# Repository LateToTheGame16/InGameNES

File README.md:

# InGameNES
 NES console that fits in a game cart

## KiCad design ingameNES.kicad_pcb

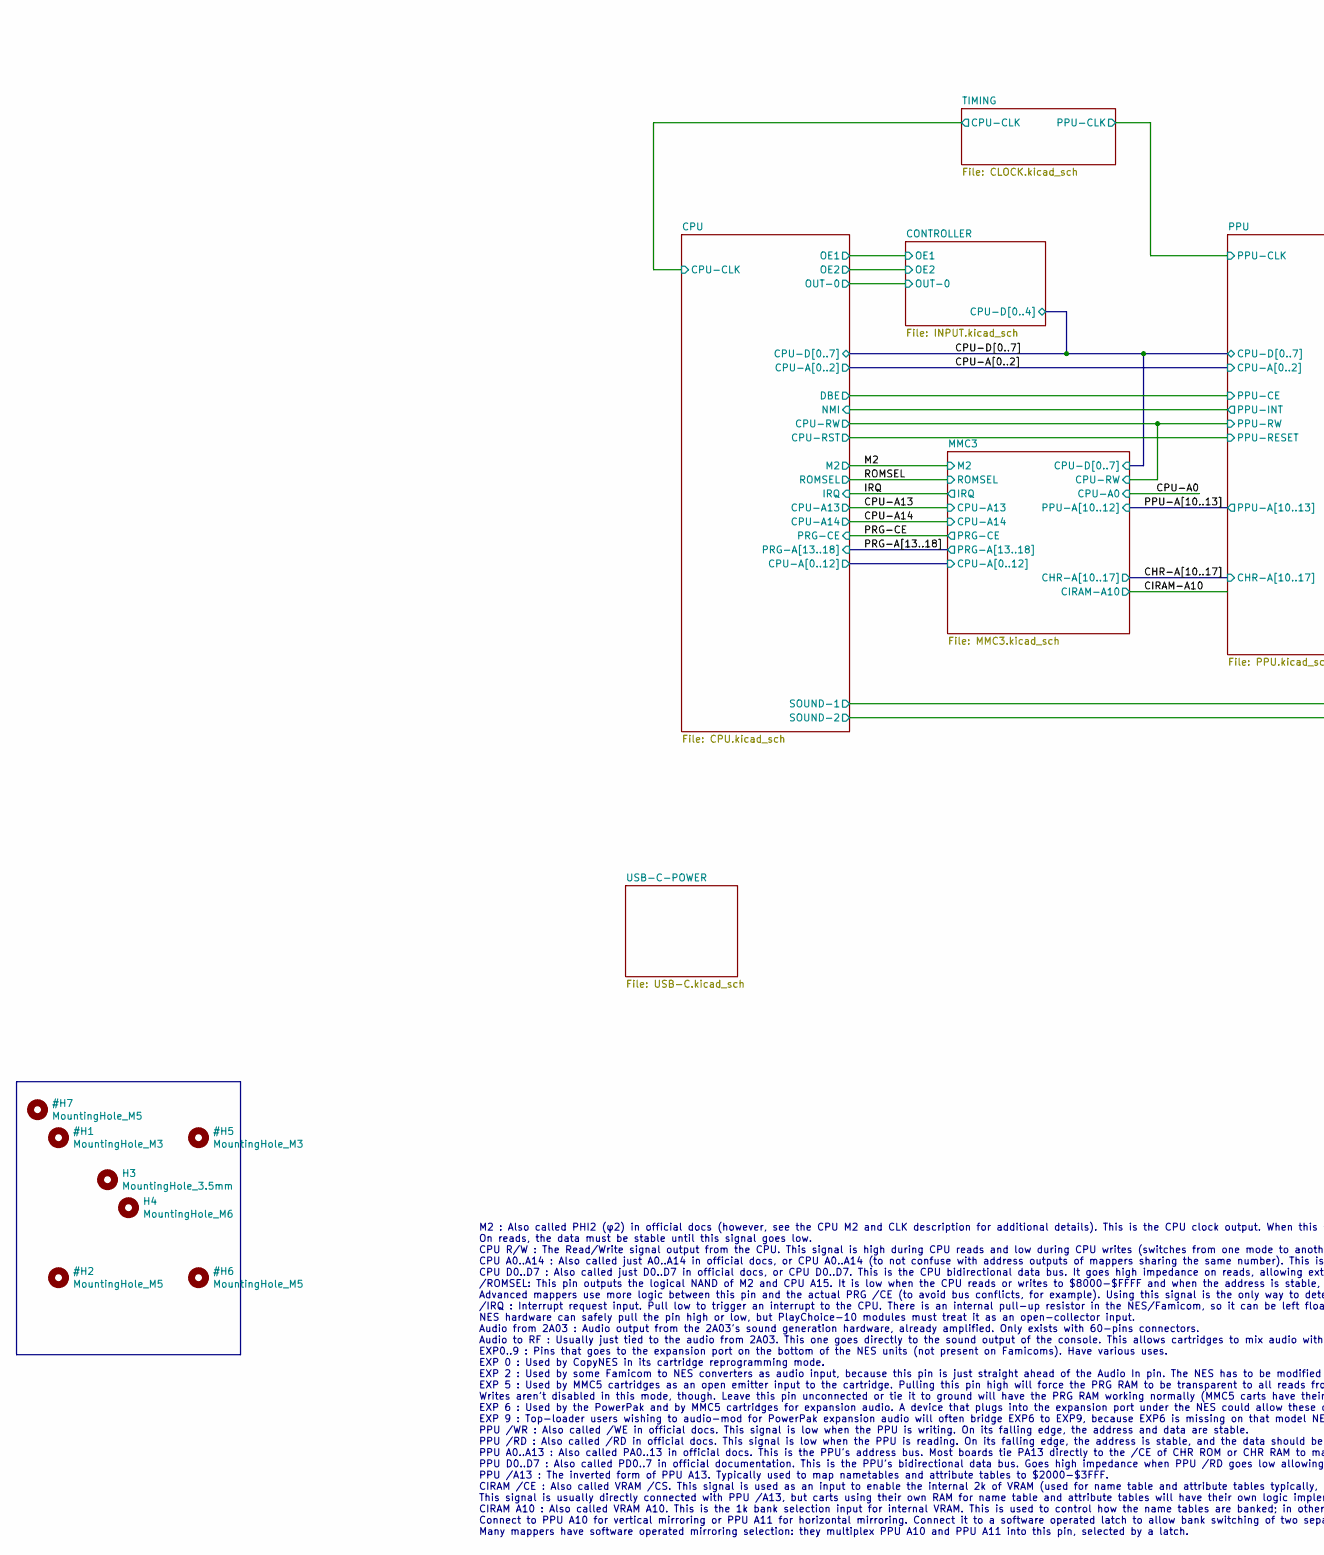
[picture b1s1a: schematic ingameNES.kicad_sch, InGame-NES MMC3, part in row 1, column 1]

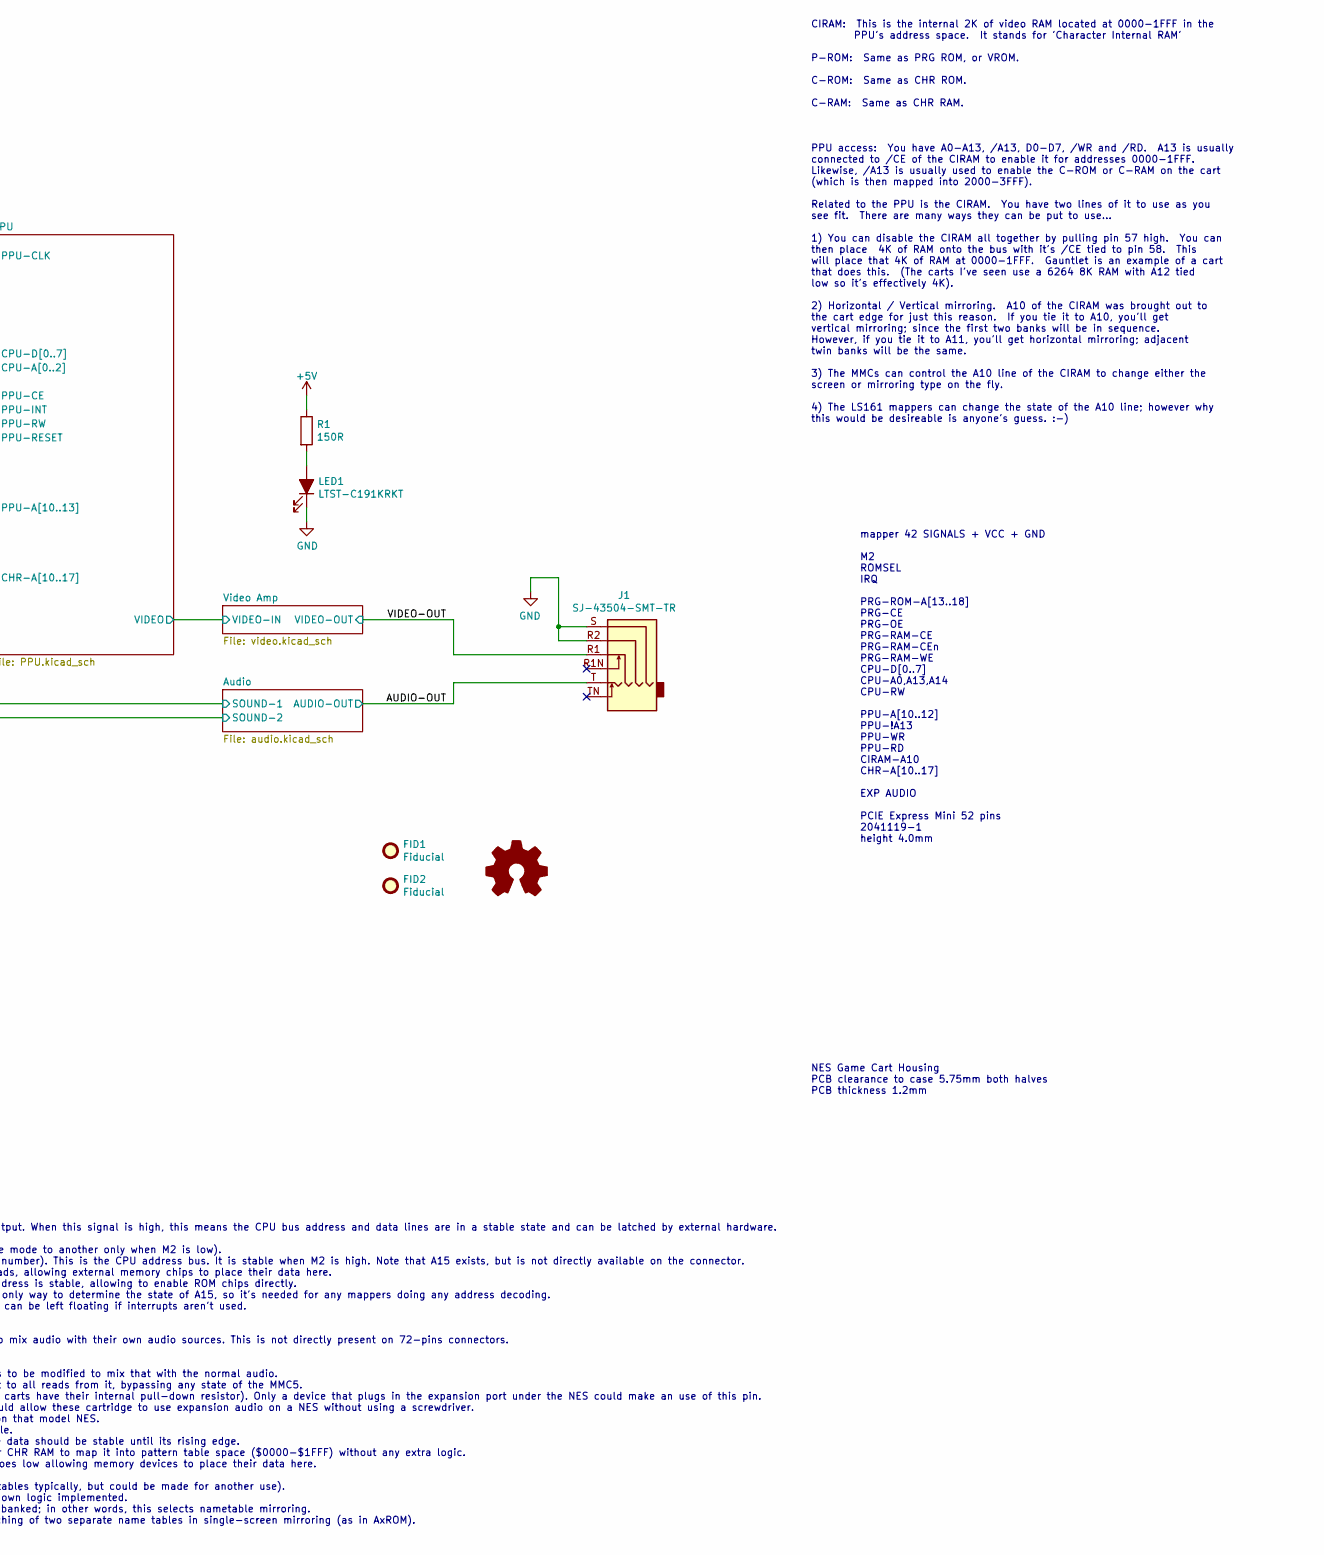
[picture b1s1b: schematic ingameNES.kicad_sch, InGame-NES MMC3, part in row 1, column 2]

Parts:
FID1, FID2: Fiducial; Fiducial_1.5mm_Mask3mm
H3: MountingHole_3.5mm
H4: MountingHole_M6; MountingHole_6.4mm_M6
J1: SJ-43504-SMT-TR; CUI_SJ-43504-SMT-TR; MPN SJ-43504-SMT-TR; Digikey CP-43504SJCT-ND
LED1: LTST-C191KRKT; LED_0603_1608Metric; MPN LTST-C191KRKT; Digikey 160-1447-1-ND
R1: 150R; R_0603_1608Metric; MPN RC0603FR-07150RL; Digikey 311-150HRCT-ND

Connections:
/AUDIO-OUT: J1.T; also elsewhere on the board
/VIDEO-OUT: J1.R1; also elsewhere on the board
unnamed: LED1.2 (A), R1.2

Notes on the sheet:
mapper 42 SIGNALS + VCC + GND M2 ROMSEL IRQ PRG-ROM-A[13..18] PRG-CE PRG-OE PRG-RAM-CE PRG-RAM-CEn PRG-RAM-WE CPU-D[0..7] CPU-A0,A13,A14 CPU-RW PPU-A[10..12] PPU-!A13 PPU-WR PPU-RD CIRAM-A10 CHR-A[10..17] EXP AUDIO PCIE Express Mini 52 pins 2041119-1 height 4.0mm
CIRAM: This is the internal 2K of video RAM located at 0000-1FFF in the PPU's address space. It stands for 'Character Internal RAM' P-ROM: Same as PRG ROM, or VROM. C-ROM: Same as CHR ROM. C-RAM: Same as CHR RAM. PPU access: You have A0-A13, /A13, D0-D7, /WR and /RD. A13 is usually connected to /CE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
M2 : Also called PHI2 (φ2) in official docs (however, see the CPU M2 and CLK description for additional details). This is the CPU clock output. When this signal is high, this means the CPU bus address and data lines are in a stable state and can be latched by external hardware. On reads, the data m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
NES Game Cart Housing PCB clearance to case 5.75mm both halves PCB thickness 1.2mm

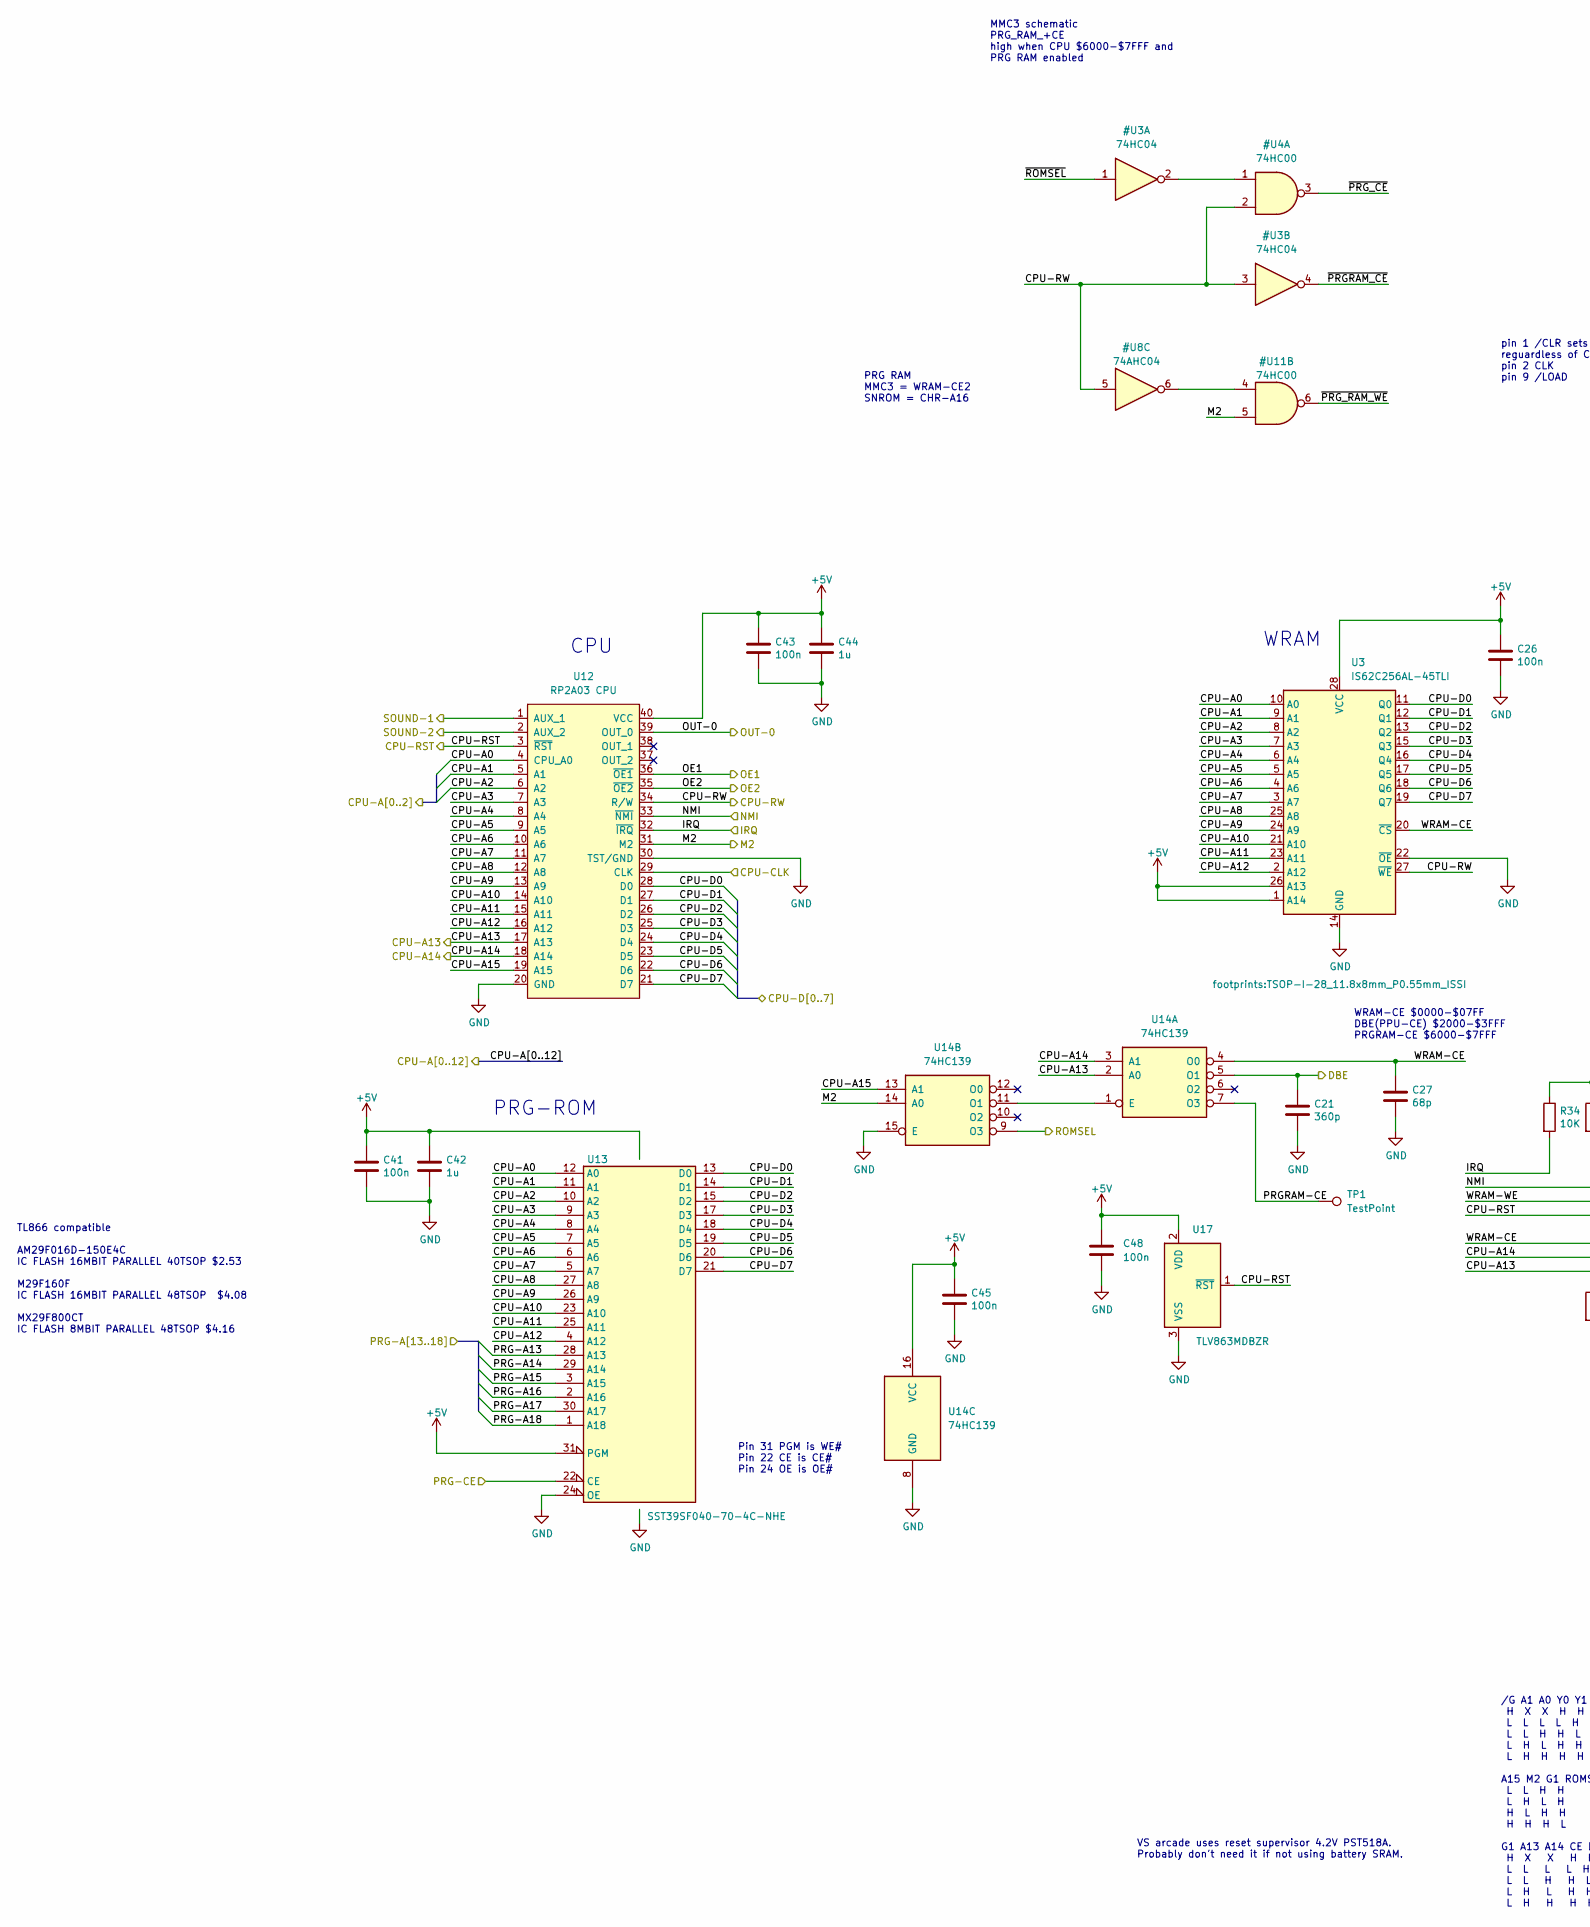
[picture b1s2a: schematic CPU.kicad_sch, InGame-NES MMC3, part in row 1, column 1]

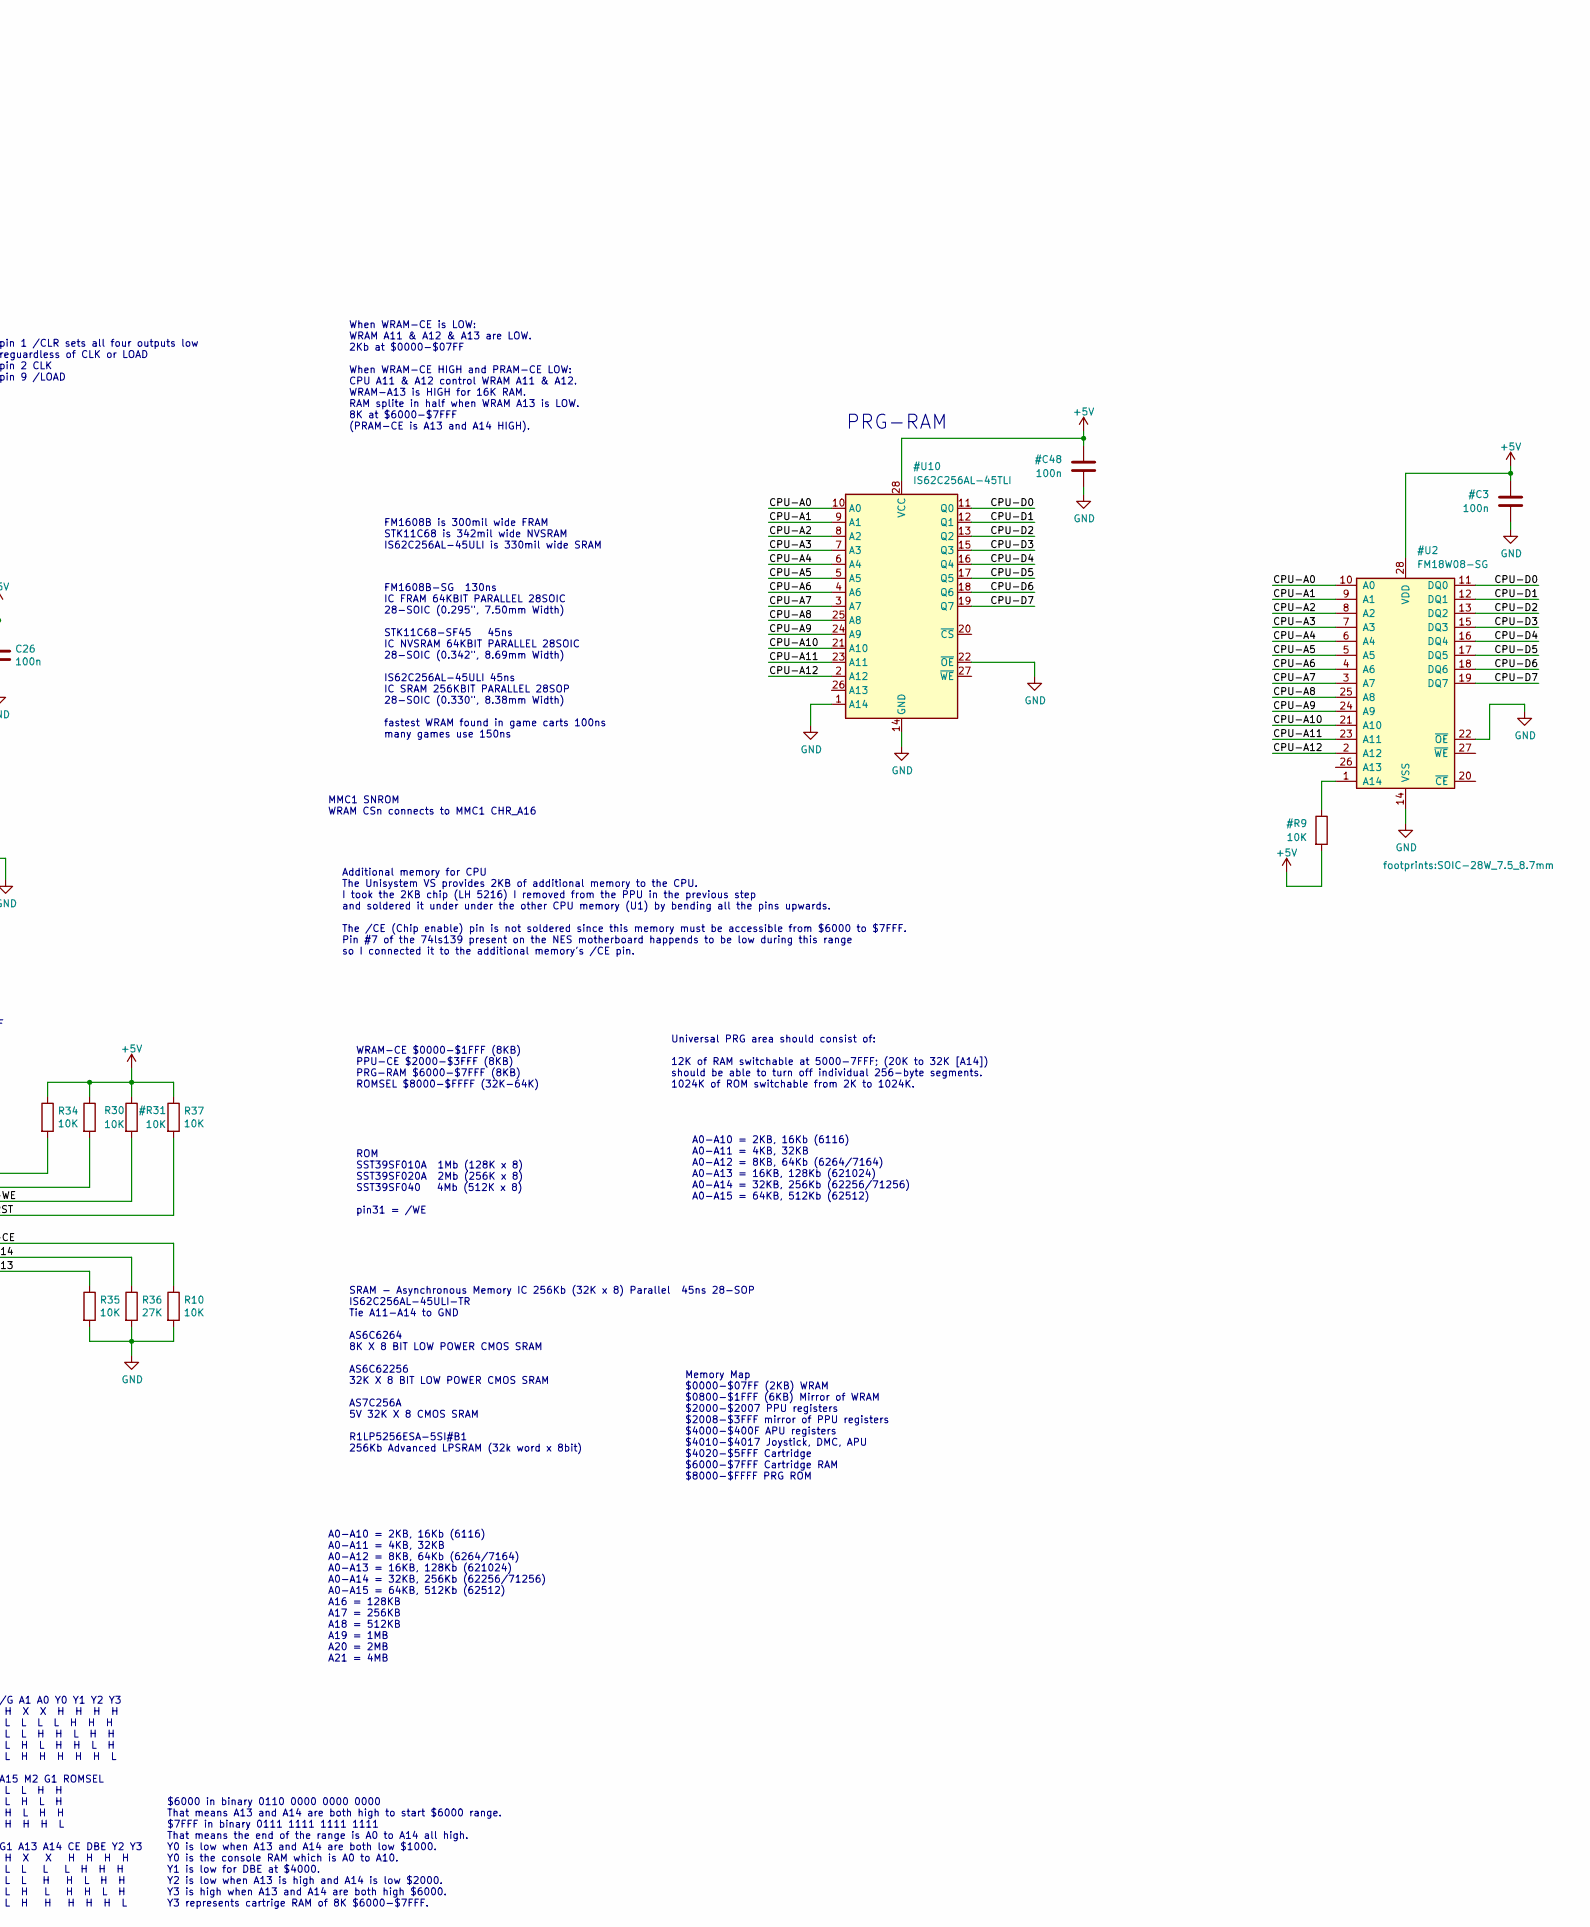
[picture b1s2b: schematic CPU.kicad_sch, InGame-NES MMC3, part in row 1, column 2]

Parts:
C21: 360p; C_0603_1608Metric; MPN C0603C361J5GAC7867; Digikey 399-15397-1-ND
C26, C41, C43, C45, C48: 100n; C_0402_1005Metric; MPN CL05B104KO5NNWC; Digikey 1276-1509-2-ND
C27: 68p; C_0402_1005Metric; MPN CC0402JRNPO9BN680; Digikey 311-1340-1-ND
C42, C44: 1u; C_0402_1005Metric; MPN GRM155R61A105KE15D; Digikey 490-3890-2-ND
R10, R30, R34, R35, R37: 10K; R_0402_1005Metric; MPN ERJ-2RKF1002X; Digikey P10.0KLCT-ND
R36: 27K; R_0402_1005Metric; MPN RC0402JR-0727KL; Digikey 311-27KJRCT-ND
TP1: TestPoint; TestPoint_Pad_D1.5mm
U3: IS62C256AL-45TLI; TSOP-I-28_11.8x8mm_P0.55mm_ISSI; MPN IS62C256AL-45TLI; Digikey 706-1109-ND
U12: RP2A03 CPU; DIP-40_W15.24mm; MPN ED40DT; Digikey ED3048-5-ND
U13: SST39SF040-70-4C-NHE; SOCKET-PLCC-32-SMD; MPN SST39SF040-70-4C-NHE; Digikey SST39SF040-70-4C-NHE-ND
U14: 74HC139; TSSOP-16_4.4x5mm_P0.65mm; MPN SN74HC139PWR; Digikey 296-8231-1-ND
U17: TLV863MDBZR; SOT-23; MPN TLV863MDBZR; Digikey 296-29707-1-ND

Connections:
/Audio/SOUND-1: U12.1 (AUX_1); also elsewhere on the board
/Audio/SOUND-2: U12.2 (AUX_2); also elsewhere on the board
/CONTROLLER/OE1: U12.36 (~OE1); also elsewhere on the board
/CONTROLLER/OE2: U12.35 (~OE2); also elsewhere on the board
/CONTROLLER/OUT-0: U12.39 (OUT_0); also elsewhere on the board
/CPU/CPU-A15: U12.19 (A15), U14.13 (A1)
/CPU/CPU-RST: R37.2, U12.3 (~RST), U17.1 (~RST); also elsewhere on the board
/CPU/DBE: C21.2, U14.5 (O1); also elsewhere on the board
/CPU/NMI: R30.2, U12.33 (~NMI); also elsewhere on the board
/CPU/PRGRAM-CE: TP1.1, U14.7 (O3)
/CPU/WRAM-CE: C27.2, R10.1, U3.20 (~CS), U14.4 (O0)
unnamed: U14.1 (E), U14.11 (O1)

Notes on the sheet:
FM1608B-SG 130ns IC FRAM 64KBIT PARALLEL 28SOIC 28-SOIC (0.295", 7.50mm Width) STK11C68-SF45 45ns IC NVSRAM 64KBIT PARALLEL 28SOIC 28-SOIC (0.342", 8.69mm Width) IS62C256AL-45ULI 45ns IC SRAM 256KBIT PARALLEL 28SOP 28-SOIC (0.330", 8.38mm Width) fastest WRAM found in game carts 100ns many games use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
PRG RAM MMC3 = WRAM-CE2 SNROM = CHR-A16
PRG-ROM
CPU
TL866 compatible AM29F016D-150E4C IC FLASH 16MBIT PARALLEL 40TSOP $2.53 M29F160F IC FLASH 16MBIT PARALLEL 48TSOP $4.08 MX29F800CT IC FLASH 8MBIT PARALLEL 48TSOP $4.16
pin 1 /CLR sets all four outputs low reguardless of CLK or LOAD pin 2 CLK pin 9 /LOAD
Additional memory for CPU The Unisystem VS provides 2KB of additional memory to the CPU. I took the 2KB chip (LH 5216) I removed from the PPU in the previous step and soldered it under under the other CPU memory (U1) by bending all the pins upwards. The /CE (Chip enable) pin is not soldered since t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
ROM SST39SF010A 1Mb (128K x 8) SST39SF020A 2Mb (256K x 8) SST39SF040 4Mb (512K x 8) pin31 = /WE
Memory Map $0000-$07FF (2KB) WRAM $0800-$1FFF (6KB) Mirror of WRAM $2000-$2007 PPU registers $2008-$3FFF mirror of PPU registers $4000-$400F APU registers $4010-$4017 Joystick, DMC, APU $4020-$5FFF Cartridge $6000-$7FFF Cartridge RAM $8000-$FFFF PRG ROM
Pin 31 PGM is WE# Pin 22 CE is CE# Pin 24 OE is OE#
VS arcade uses reset supervisor 4.2V PST518A. Probably don't need it if not using battery SRAM.
PRG-RAM
Universal PRG area should consist of: 12K of RAM switchable at 5000-7FFF; (20K to 32K [A14]) should be able to turn off individual 256-byte segments. 1024K of ROM switchable from 2K to 1024K.
WRAM-CE $0000-$07FF DBE(PPU-CE) $2000-$3FFF PRGRAM-CE $6000-$7FFF
$6000 in binary 0110 0000 0000 0000 That means A13 and A14 are both high to start $6000 range. $7FFF in binary 0111 1111 1111 1111 That means the end of the range is A0 to A14 all high. Y0 is low when A13 and A14 are both low $1000. Y0 is the console RAM which is A0 to A10. Y1 is low for DBE at $40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
When WRAM-CE is LOW: WRAM A11 & A12 & A13 are LOW. 2Kb at $0000-$07FF When WRAM-CE HIGH and PRAM-CE LOW: CPU A11 & A12 control WRAM A11 & A12. WRAM-A13 is HIGH for 16K RAM. RAM splite in half when WRAM A13 is LOW. 8K at $6000-$7FFF (PRAM-CE is A13 and A14 HIGH).
WRAM
SRAM - Asynchronous Memory IC 256Kb (32K x 8) Parallel 45ns 28-SOP IS62C256AL-45ULI-TR Tie A11-A14 to GND AS6C6264 8K X 8 BIT LOW POWER CMOS SRAM AS6C62256 32K X 8 BIT LOW POWER CMOS SRAM AS7C256A 5V 32K X 8 CMOS SRAM R1LP5256ESA-5SI#B1 256Kb Advanced LPSRAM (32k word x 8bit)
MMC3 schematic PRG_RAM_+CE high when CPU $6000-$7FFF and PRG RAM enabled
FM1608B is 300mil wide FRAM STK11C68 is 342mil wide NVSRAM IS62C256AL-45ULI is 330mil wide SRAM
WRAM-CE $0000-$1FFF (8KB) PPU-CE $2000-$3FFF (8KB) PRG-RAM $6000-$7FFF (8KB) ROMSEL $8000-$FFFF (32K-64K)
/G A1 A0 Y0 Y1 Y2 Y3 H X X H H H H L L L L H H H L L H H L H H L H L H H L H L H H H H H L A15 M2 G1 ROMSEL L L H H L H L H H L H H H H H L G1 A13 A14 CE DBE Y2 Y3 H X X H H H H L L L L H H H L L H H L H H L H L H H L H L H H H H H L
A0-A10 = 2KB, 16Kb (6116) A0-A11 = 4KB, 32KB A0-A12 = 8KB, 64Kb (6264/7164) A0-A13 = 16KB, 128Kb (621024) A0-A14 = 32KB, 256Kb (62256/71256) A0-A15 = 64KB, 512Kb (62512) A16 = 128KB A17 = 256KB A18 = 512KB A19 = 1MB A20 = 2MB A21 = 4MB
A0-A10 = 2KB, 16Kb (6116) A0-A11 = 4KB, 32KB A0-A12 = 8KB, 64Kb (6264/7164) A0-A13 = 16KB, 128Kb (621024) A0-A14 = 32KB, 256Kb (62256/71256) A0-A15 = 64KB, 512Kb (62512)
MMC1 SNROM WRAM CSn connects to MMC1 CHR_A16

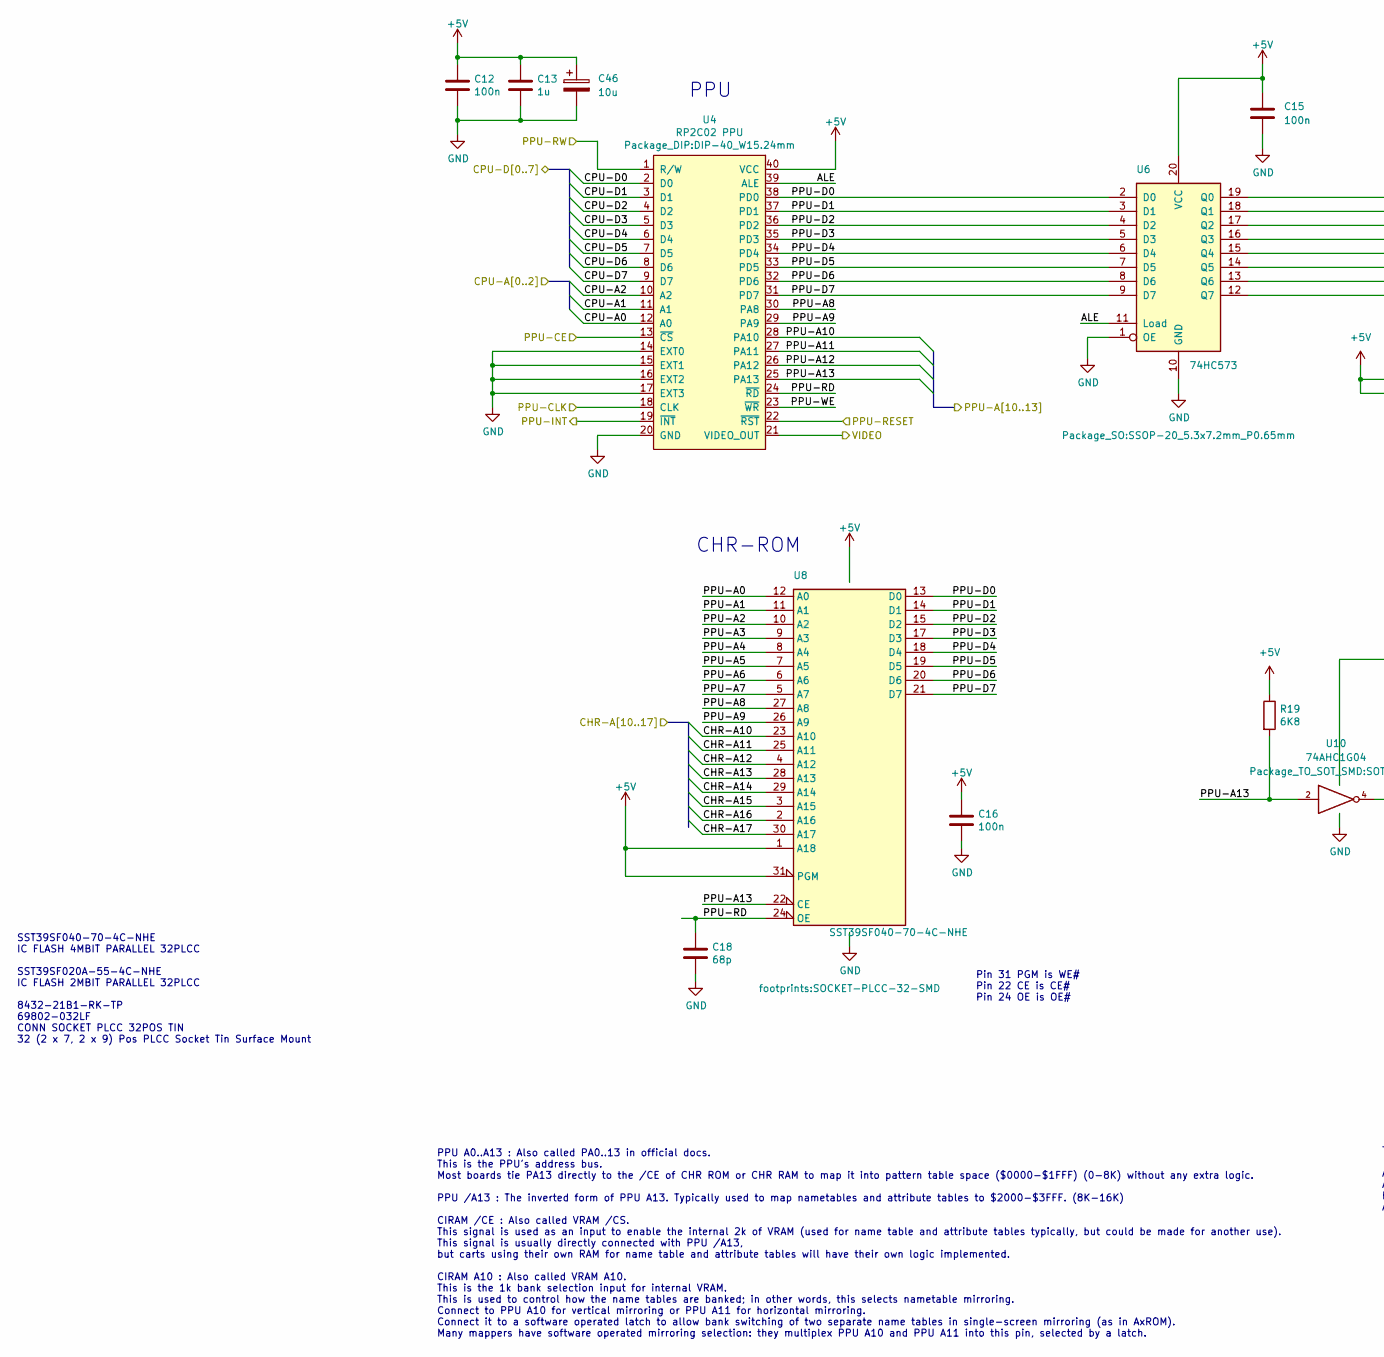
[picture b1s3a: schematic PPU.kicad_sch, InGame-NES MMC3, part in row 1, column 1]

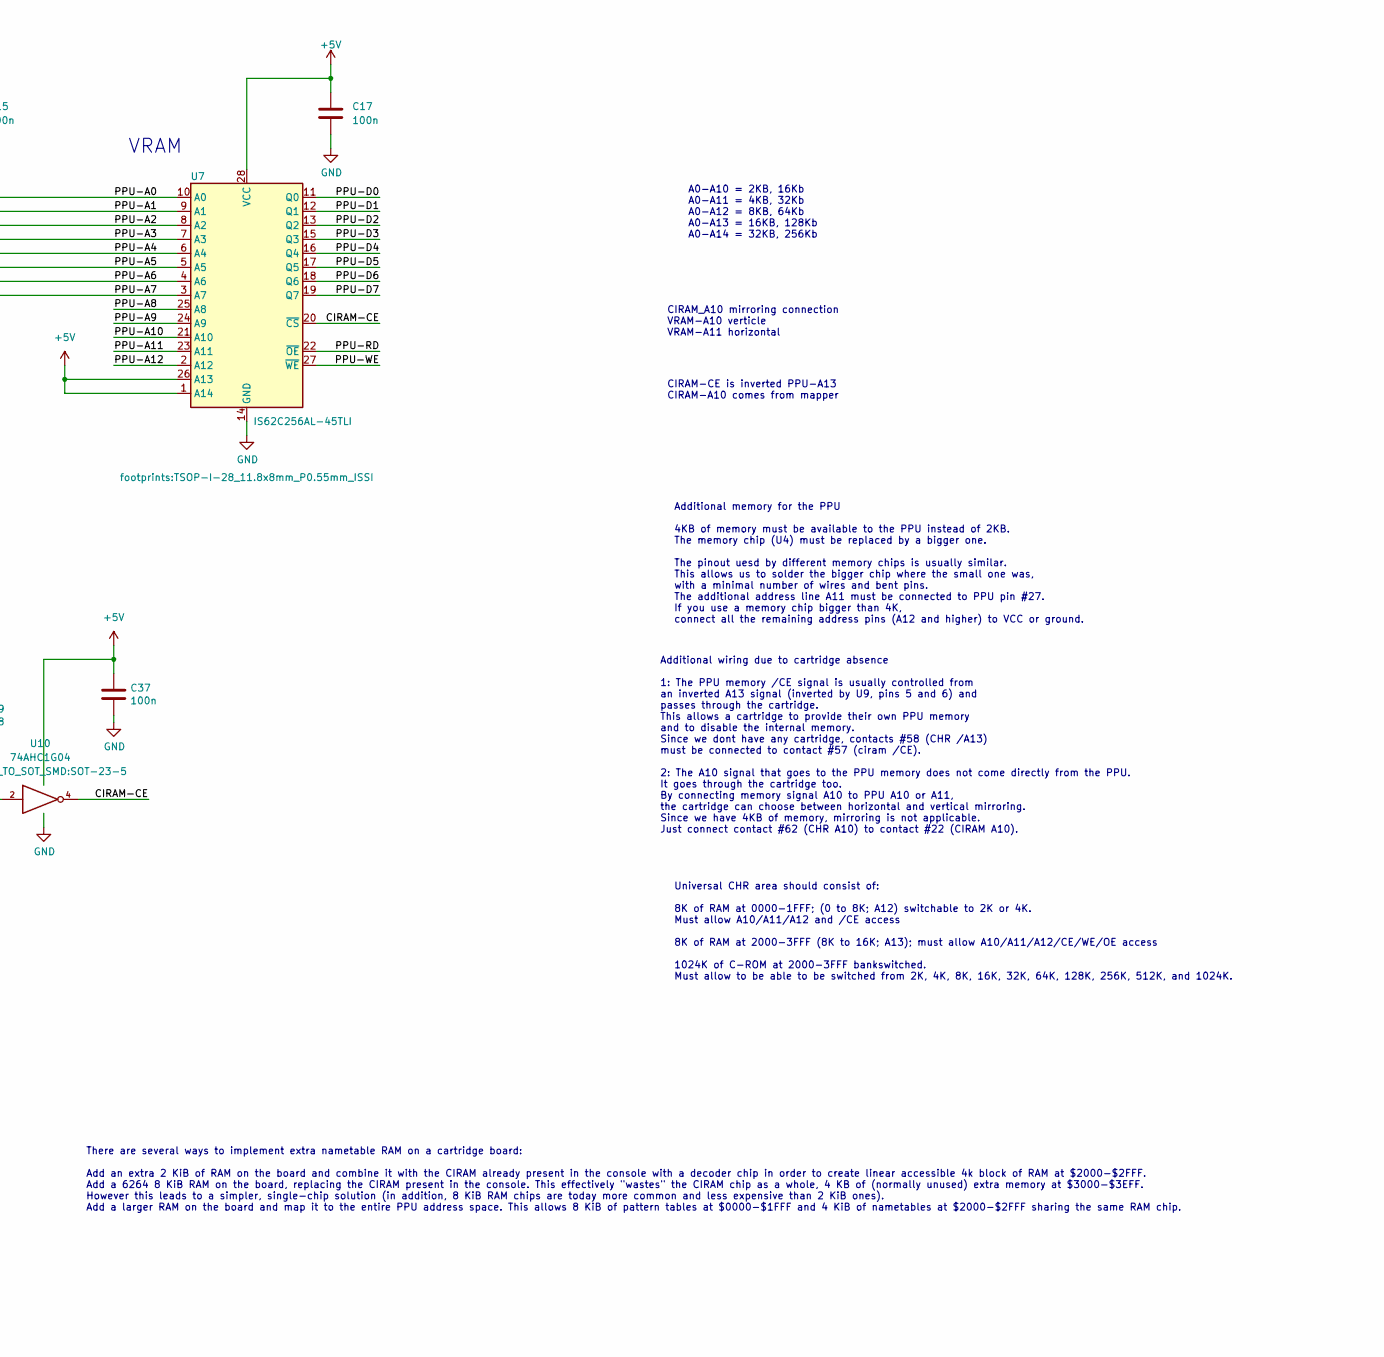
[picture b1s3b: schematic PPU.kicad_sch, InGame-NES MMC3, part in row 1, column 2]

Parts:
C12, C15, C16, C17, C37: 100n; C_0402_1005Metric; MPN CL05B104KO5NNWC; Digikey 1276-1509-2-ND
C13: 1u; C_0402_1005Metric; MPN GRM155R61A105KE15D; Digikey 490-3890-2-ND
C18: 68p; C_0402_1005Metric; MPN CC0402JRNPO9BN680; Digikey 311-1340-1-ND
C46: 10u; CP_EIA-3216-18_Kemet-A; MPN T491A106K010AT; Digikey 399-3684-1-ND
R19: 6K8; R_0402_1005Metric; MPN RC0402FR-076K8L; Digikey 311-6.80KLRCT-ND
U4: RP2C02 PPU; DIP-40_W15.24mm; MPN ED40DT; Digikey ED3048-5-ND
U6: 74HC573; SSOP-20_5.3x7.2mm_P0.65mm; MPN SN74HC573ADBR; Digikey 296-SN74HC573ADBRCT-ND
U7: IS62C256AL-45TLI; TSOP-I-28_11.8x8mm_P0.55mm_ISSI; MPN IS62C256AL-45TLI; Digikey 706-1109-ND
U8: SST39SF040-70-4C-NHE; SOCKET-PLCC-32-SMD; MPN SST39SF040-70-4C-NHE; Digikey SST39SF040-70-4C-NHE-ND
U10: 74AHC1G04; SOT-23-5; MPN SN74AHC1G04DBVR; Digikey 296-1089-1-ND

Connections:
/CPU/CPU-RST: U4.22 (~RST); also elsewhere on the board
/CPU/DBE: U4.13 (~CS); also elsewhere on the board
/CPU/NMI: U4.19 (~INT); also elsewhere on the board
/PPU-A13: R19.2, U4.25 (PA13), U8.22 (CE), U10.2
/PPU/ALE: U4.39 (ALE), U6.11 (Load)
/PPU/CIRAM-CE: U7.20 (~CS), U10.4
/PPU/PPU-A0: U6.19 (Q0), U7.10 (A0), U8.12 (A0)
/PPU/PPU-A1: U6.18 (Q1), U7.9 (A1), U8.11 (A1)
/PPU/PPU-A2: U6.17 (Q2), U7.8 (A2), U8.10 (A2)
/PPU/PPU-A3: U6.16 (Q3), U7.7 (A3), U8.9 (A3)
/PPU/PPU-A4: U6.15 (Q4), U7.6 (A4), U8.8 (A4)
/PPU/PPU-A5: U6.14 (Q5), U7.5 (A5), U8.7 (A5)
/PPU/PPU-A6: U6.13 (Q6), U7.4 (A6), U8.6 (A6)
/PPU/PPU-A7: U6.12 (Q7), U7.3 (A7), U8.5 (A7)
/PPU/PPU-A8: U4.30 (PA8), U7.25 (A8), U8.27 (A8)
/PPU/PPU-A9: U4.29 (PA9), U7.24 (A9), U8.26 (A9)
/PPU/PPU-D0: U4.38 (PD0), U6.2 (D0), U7.11 (Q0), U8.13 (D0)
/PPU/PPU-D1: U4.37 (PD1), U6.3 (D1), U7.12 (Q1), U8.14 (D1)
/PPU/PPU-D2: U4.36 (PD2), U6.4 (D2), U7.13 (Q2), U8.15 (D2)
/PPU/PPU-D3: U4.35 (PD3), U6.5 (D3), U7.15 (Q3), U8.17 (D3)
/PPU/PPU-D4: U4.34 (PD4), U6.6 (D4), U7.16 (Q4), U8.18 (D4)
/PPU/PPU-D5: U4.33 (PD5), U6.7 (D5), U7.17 (Q5), U8.19 (D5)
/PPU/PPU-D6: U4.32 (PD6), U6.8 (D6), U7.18 (Q6), U8.20 (D6)
/PPU/PPU-D7: U4.31 (PD7), U6.9 (D7), U7.19 (Q7), U8.21 (D7)
/PPU/PPU-RD: C18.2, U4.24 (~RD), U7.22 (~OE), U8.24 (OE)
/PPU/PPU-WE: U4.23 (~WR), U7.27 (~WE)
/PPU/VIDEO: U4.21 (VIDEO_OUT); also elsewhere on the board

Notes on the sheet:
SST39SF040-70-4C-NHE IC FLASH 4MBIT PARALLEL 32PLCC SST39SF020A-55-4C-NHE IC FLASH 2MBIT PARALLEL 32PLCC 8432-21B1-RK-TP 69802-032LF CONN SOCKET PLCC 32POS TIN 32 (2 x 7, 2 x 9) Pos PLCC Socket Tin Surface Mount
A0-A10 = 2KB, 16Kb A0-A11 = 4KB, 32Kb A0-A12 = 8KB, 64Kb A0-A13 = 16KB, 128Kb A0-A14 = 32KB, 256Kb
Additional wiring due to cartridge absence 1: The PPU memory /CE signal is usually controlled from an inverted A13 signal (inverted by U9, pins 5 and 6) and passes through the cartridge. This allows a cartridge to provide their own PPU memory and to disable the internal memory. Since we dont have a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
CIRAM_A10 mirroring connection VRAM-A10 verticle VRAM-A11 horizontal
Additional memory for the PPU 4KB of memory must be available to the PPU instead of 2KB. The memory chip (U4) must be replaced by a bigger one. The pinout uesd by different memory chips is usually similar. This allows us to solder the bigger chip where the small one was, with a minimal number of wi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
CHR-ROM
Universal CHR area should consist of: 8K of RAM at 0000-1FFF; (0 to 8K; A12) switchable to 2K or 4K. Must allow A10/A11/A12 and /CE access 8K of RAM at 2000-3FFF (8K to 16K; A13); must allow A10/A11/A12/CE/WE/OE access 1024K of C-ROM at 2000-3FFF bankswitched. Must allow to be able to be switched f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
PPU A0..A13 : Also called PA0..13 in official docs. This is the PPU's address bus. Most boards tie PA13 directly to the /CE of CHR ROM or CHR RAM to map it into pattern table space ($0000-$1FFF) (0-8K) without any extra logic. PPU /A13 : The inverted form of PPU A13. Typically used to map nametable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
There are several ways to implement extra nametable RAM on a cartridge board: Add an extra 2 KiB of RAM on the board and combine it with the CIRAM already present in the console with a decoder chip in order to create linear accessible 4k block of RAM at $2000-$2FFF. Add a 6264 8 KiB RAM on the boar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
CIRAM-CE is inverted PPU-A13 CIRAM-A10 comes from mapper
PPU
VRAM
Pin 31 PGM is WE# Pin 22 CE is CE# Pin 24 OE is OE#

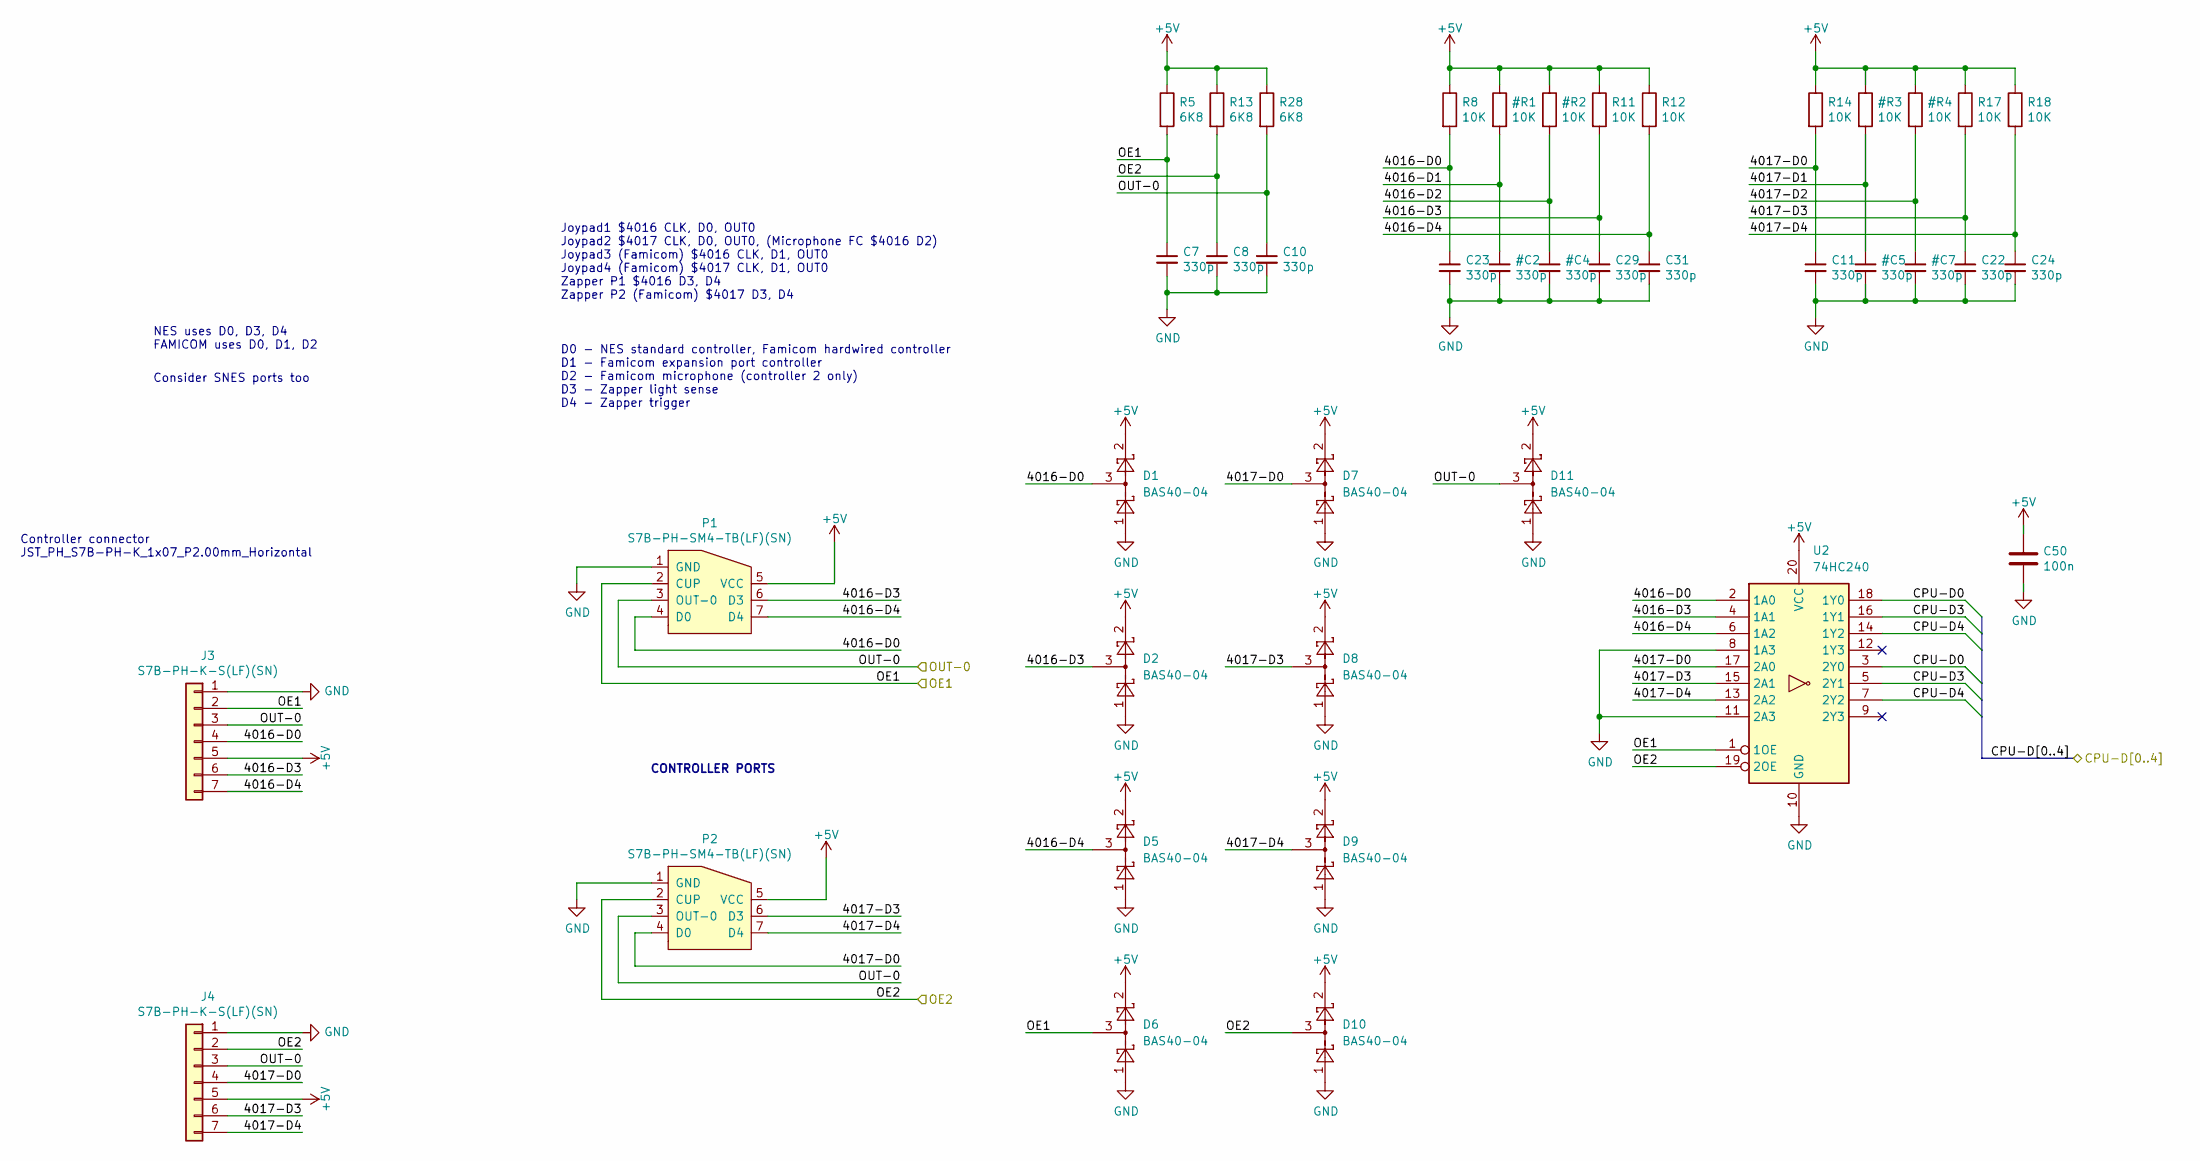
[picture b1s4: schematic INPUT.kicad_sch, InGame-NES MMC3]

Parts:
C7, C8, C10, C11, C22, C23, C24, C29, C31: 330p; C_0402_1005Metric; MPN 0402N331J500CT; Digikey 1292-1308-1-ND
C50: 100n; C_0402_1005Metric; MPN CL05B104KO5NNWC; Digikey 1276-1509-2-ND
D1, D2, D5, D6, D7, D8, D9, D10, D11: BAS40-04; SOT-23; MPN BAS40-04-TP; Digikey BAS40-04TPMSCT-ND
J3, J4: S7B-PH-K-S(LF)(SN); JST_PH_S7B-PH-K_1x07_P2.00mm_Horizontal; MPN S7B-PH-K-S(LF)(SN); Digikey 455-1724-ND
P1, P2: S7B-PH-SM4-TB(LF)(SN); JST_PH_S7B-PH-SM4-TB_1x07-1MP_P2.00mm_Horizontal; MPN S7B-PH-SM4-TB(LF)(SN); Digikey 455-1754-1-ND
R5, R13, R28: 6K8; R_0402_1005Metric; MPN RC0402FR-076K8L; Digikey 311-6.80KLRCT-ND
R8, R11, R12, R14, R17, R18: 10K; R_0402_1005Metric; MPN ERJ-2RKF1002X; Digikey P10.0KLCT-ND
U2: 74HC240; TSSOP-20_4.4x6.5mm_P0.65mm; MPN SN74HC240PWR; Digikey 296-8269-1-ND

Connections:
/CONTROLLER/4016-D0: C23.1, D1.3, J3.4, P1.4 (D0), R8.2, U2.2 (1A0)
/CONTROLLER/4016-D3: C29.1, D2.3, J3.6, P1.6 (D3), R11.2, U2.4 (1A1)
/CONTROLLER/4016-D4: C31.1, D5.3, J3.7, P1.7 (D4), R12.2, U2.6 (1A2)
/CONTROLLER/4017-D0: C11.1, D7.3, J4.4, P2.4 (D0), R14.2, U2.17 (2A0)
/CONTROLLER/4017-D3: C22.1, D8.3, J4.6, P2.6 (D3), R17.2, U2.15 (2A1)
/CONTROLLER/4017-D4: C24.1, D9.3, J4.7, P2.7 (D4), R18.2, U2.13 (2A2)
/CONTROLLER/OE1: C7.1, D6.3, J3.2, P1.2 (CUP), R5.2, U2.1 (1OE); also elsewhere on the board
/CONTROLLER/OE2: C8.1, D10.3, J4.2, P2.2 (CUP), R13.2, U2.19 (2OE); also elsewhere on the board
/CONTROLLER/OUT-0: C10.1, D11.3, J3.3, J4.3, P1.3 (OUT-0), P2.3 (OUT-0), R28.2; also elsewhere on the board

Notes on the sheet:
Joypad1 $4016 CLK, D0, OUT0 Joypad2 $4017 CLK, D0, OUT0, (Microphone FC $4016 D2) Joypad3 (Famicom) $4016 CLK, D1, OUT0 Joypad4 (Famicom) $4017 CLK, D1, OUT0 Zapper P1 $4016 D3, D4 Zapper P2 (Famicom) $4017 D3, D4
CONTROLLER PORTS
NES uses D0, D3, D4 FAMICOM uses D0, D1, D2
D0 - NES standard controller, Famicom hardwired controller D1 - Famicom expansion port controller D2 - Famicom microphone (controller 2 only) D3 - Zapper light sense D4 - Zapper trigger
Controller connector JST_PH_S7B-PH-K_1x07_P2.00mm_Horizontal
Consider SNES ports too
